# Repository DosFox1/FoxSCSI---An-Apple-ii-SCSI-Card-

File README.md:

# FoxSCSI - An Apple ii SCSI Card 
An open source clone of the Apple ii SCSI Card. Through hole and done in two layers!

(Many thanks to HKZ for testing this VDEV1 Prototype design)

# So what is it?

This is a recreation of the original Apple SCSI Rev C Card for the Apple II.
The equations for the SCSI card were found, converted to GALs, and tested with an original Rev C card.

Additionally, the schematics and ROM for the Rev C card are available online (added in this repository for completeness).
This board is two layer to reduce costs (five boards, finished in ENIG should be about £30 or £6 per board), and is fully through hole.
A 2.85v active termination voltage regulator is added but is not required. 

HKZ is working on an SMD variant of the SCSI card:
https://codeberg.org/hkzlab/AppleII_SCSI_RevC_schematics

# Note Regarding the Board Status
The initial VDEV1 board was tested by HKZ, and three issues were found:
1) a missing connection from IOSEL to the 74LS08
2) A missing "ghost" 330pf capacitor present on the actual boards, but not the transcribed schematics
3) Capacitors were initially noted to be 33pf, actual values should be 330pf.

With these changes, the board successfully booted a DELTA (Apple IIe clone using GALs in place of custom logic - https://codeberg.org/hkzlab/NE_Delta_Schematics).
The latest gerbers have fixes these issues, and should work as is. 

NOTE THAT THEY HAVE NOT BEEN BUILT YET. YOUR MILEAGE MAY VARY!

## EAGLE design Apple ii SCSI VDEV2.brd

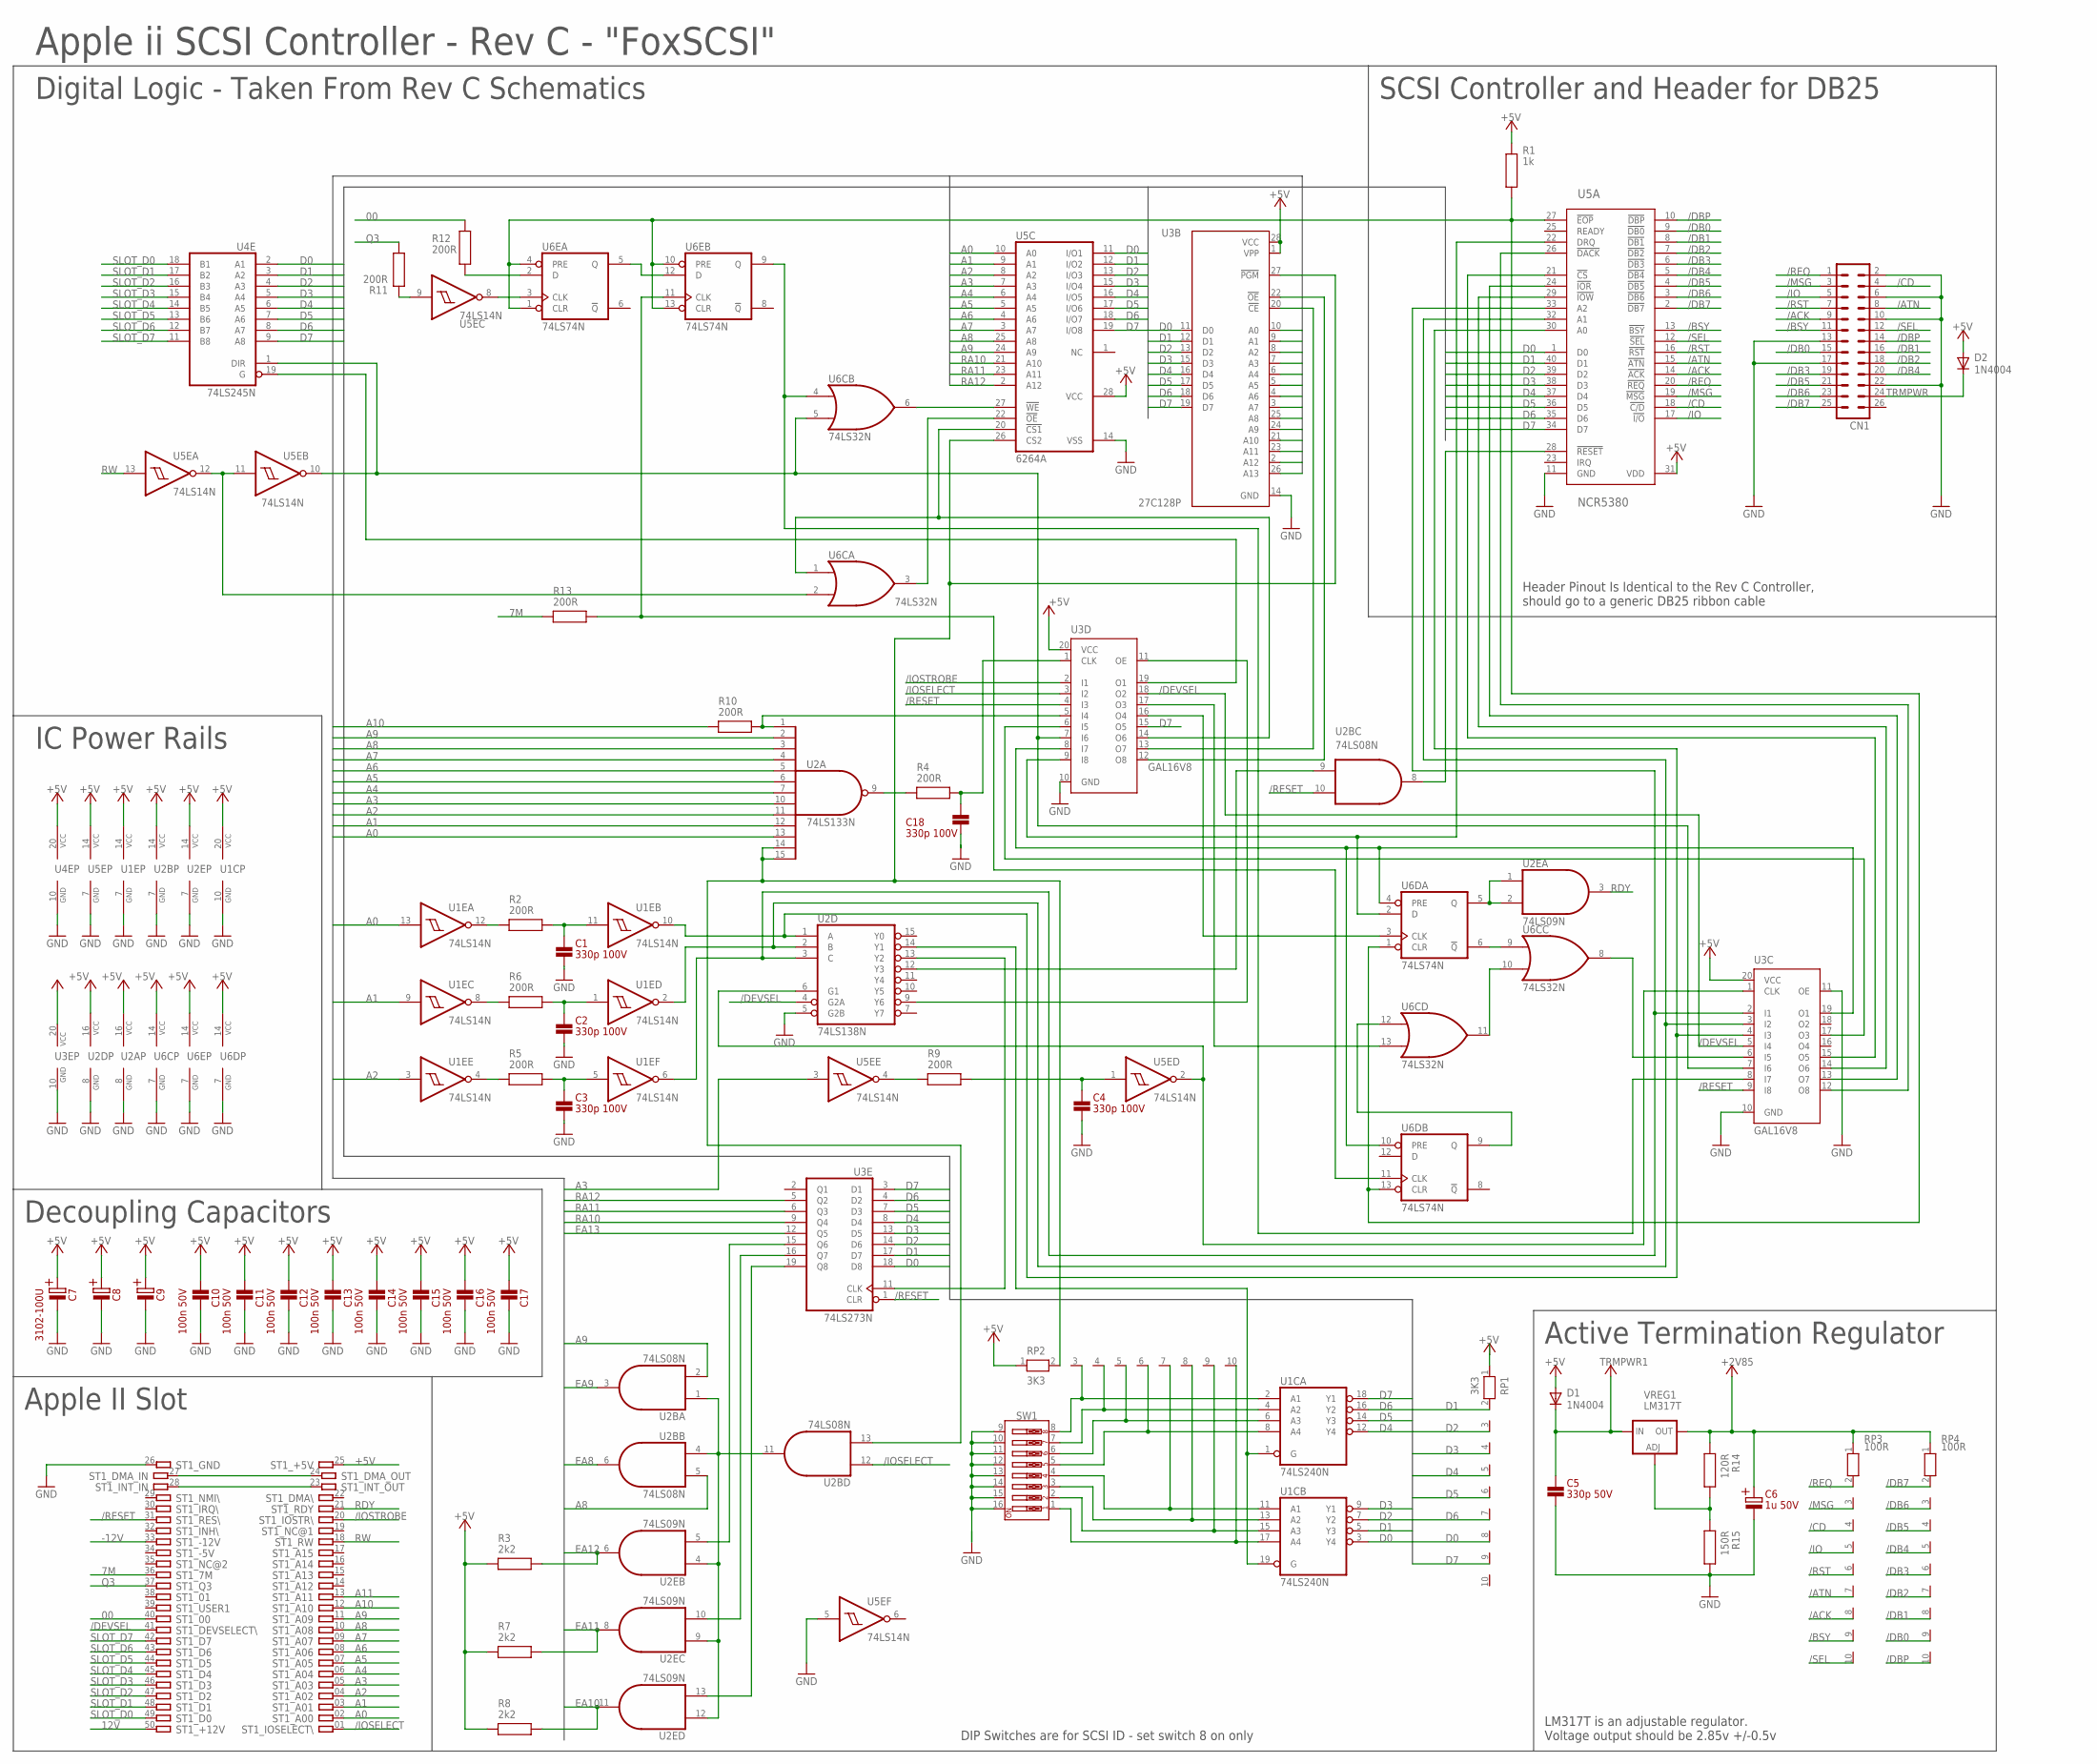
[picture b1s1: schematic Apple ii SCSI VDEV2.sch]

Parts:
C1, C2, C3, C4, C18: 330p 100V; CAP_5.08MM_PITCH
C5: 330p 50V; CAP_5.08MM_PITCH
C6: 1u 50V; CAP_ELECTROLYTIC_FLAT
C7: 3102-100U; CAP_ELECTROLYTIC_FLAT
C8, C9: 10U_TH_ELEC_CAPHORIZONTAL; CAP_ELECTROLYTIC_FLAT
C10, C11, C12, C13, C14, C15, C16, C17: 100n 50V; CAP_5.08MM_PITCH
CN1: MA13-2
D1, D2: 1N4004; DO41-10
R1: 1k; RESISTORTHRUHOLE
R2, R4, R5, R6, R9, R10, R11, R12, R13: 200R; RESISTORTHRUHOLE
R3, R7, R8: 2k2; RESISTORTHRUHOLE
R14: 120R; RESISTORTHRUHOLE
R15: 150R; RESISTORTHRUHOLE
RP1, RP2: 3K3; RN-10
RP3, RP4: 100R; RN-10
ST1: A2-50PINMINI; A2-50PIN-MINI
SW1: DIP-08-PTH; DIPSWITCH-08
U1C: 74LS240N; DIL20
U1E, U5E: 74LS14N; DIL14
U2A: 74LS133N; DIL16
U2B: 74LS08N; DIL14
U2D: 74LS138N; DIL16
U2E: 74LS09N; DIL14
U3B: 27C128P; DIL28-6
U3C, U3D: GAL16V8; DIL20
U3E: 74LS273N; DIL20
U4E: 74LS245N; DIL20
U5A: NCR5380; DIP40
U5C: 6264A; DIL28-6
U6C: 74LS32N; DIL14
U6D, U6E: 74LS74N; DIL14
VREG1: LM317T; 317TL

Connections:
00: R12.P$2, ST1.40
7M: R13.P$1, ST1.36
12V: ST1.50
+2V85: C6.P$1, R14.P$1, RP3.1, RP4.1, VREG1.2 (OUT)
+5V: C7.P$1, C8.P$1, C9.P$1, C10.P$1, C11.P$1, C12.P$1, C13.P$1, C14.P$1, C15.P$1, C16.P$1, C17.P$1, D1.A, D2.A, R1.P$2, R3.P$1, R7.P$1, R8.P$1, RP1.1, RP2.1, ST1.25, U1C.20 (VCC), U1E.14 (VCC), U2A.16 (VCC), U2B.14 (VCC), U2D.16 (VCC), U2E.14 (VCC), U3B.1 (VPP), U3B.28 (VCC), U3C.20 (VCC), U3D.20 (VCC), U3E.20 (VCC), U4E.20 (VCC), U5A.31 (VDD), U5C.28 (VCC), U5E.14 (VCC), U6C.14 (VCC), U6D.14 (VCC), U6E.14 (VCC)
-12V: ST1.33
/ACK: CN1.9, RP3.8, U5A.14 (!ACK)
/ATN: CN1.8, RP3.7, U5A.15 (!ATN)
/BSY: CN1.11, RP3.9, U5A.13 (!BSY)
/CD: CN1.4, RP3.4, U5A.18 (!C/D)
/DB0: CN1.15, RP4.9, U5A.9 (!DB0)
/DB1: CN1.16, RP4.8, U5A.8 (!DB1)
/DB2: CN1.18, RP4.7, U5A.7 (!DB2)
/DB3: CN1.19, RP4.6, U5A.6 (!DB3)
/DB4: CN1.20, RP4.5, U5A.5 (!DB4)
/DB5: CN1.21, RP4.4, U5A.4 (!DB5)
/DB6: CN1.23, RP4.3, U5A.3 (!DB6)
/DB7: CN1.25, RP4.2, U5A.2 (!DB7)
/DBP: CN1.14, RP4.10, U5A.10 (!DBP)
/DEVSEL: ST1.41, U2D.4 (G2A), U3C.5 (I4), U3D.18 (O2)
/IO: CN1.5, RP3.5, U5A.17 (!I/O)
/IOSELECT: ST1.01, U2B.12 (I0), U3D.3 (I2)
/IOSTROBE: ST1.20, U3D.2 (I1)
/MSG: CN1.3, RP3.3, U5A.19 (!MSG)
/REQ: CN1.1, RP3.2, U5A.20 (!REQ)
/RESET: ST1.31, U2B.10 (I1), U3C.9 (I8), U3D.4 (I3), U3E.1 (CLR)
/RST: CN1.7, RP3.6, U5A.16 (!RST)
/SEL: CN1.12, RP3.10, U5A.12 (!SEL)
A0: ST1.02, U1E.13 (I), U2A.13 (I10), U3B.10 (A0), U5C.10 (A0)
A1: ST1.03, U1E.9 (I), U2A.12 (I9), U3B.9 (A1), U5C.9 (A1)
A2: ST1.04, U1E.3 (I), U2A.11 (I8), U3B.8 (A2), U5C.8 (A2)
A3: ST1.05, U2A.10 (I7), U3B.7 (A3), U5C.7 (A3), U5E.3 (I)
A4: ST1.06, U2A.7 (I6), U3B.6 (A4), U5C.6 (A4)
A5: ST1.07, U2A.6 (I5), U3B.5 (A5), U5C.5 (A5)
A6: ST1.08, U2A.5 (I4), U3B.4 (A6), U5C.4 (A6)
A7: ST1.09, U2A.4 (I3), U3B.3 (A7), U5C.3 (A7)
A8: ST1.10, U2A.3 (I2), U2B.5 (I1), U5C.25 (A8)
A9: ST1.11, U2A.2 (I1), U2B.2 (I1), U5C.24 (A9)
A10: R10.P$1, ST1.12
A11: ST1.13
D0: RP1.8, U1C.3 (Y4), U3B.11 (D0), U3E.18 (D8), U4E.2 (A1), U5A.1 (D0), U5C.11 (I/O1)
D1: RP1.2, U1C.5 (Y3), U3B.12 (D1), U3E.17 (D7), U4E.3 (A2), U5A.40 (D1), U5C.12 (I/O2)
D2: RP1.3, U1C.7 (Y2), U3B.13 (D2), U3E.14 (D6), U4E.4 (A3), U5A.39 (D2), U5C.13 (I/O3)
D3: RP1.4, U1C.9 (Y1), U3B.15 (D3), U3E.13 (D5), U4E.5 (A4), U5A.38 (D3), U5C.15 (I/O4)
D4: RP1.5, U1C.12 (Y4), U3B.16 (D4), U3E.8 (D4), U4E.6 (A5), U5A.37 (D4), U5C.16 (I/O5)
D5: RP1.6, U1C.14 (Y3), U3B.17 (D5), U3E.7 (D3), U4E.7 (A6), U5A.36 (D5), U5C.17 (I/O6)
D6: RP1.7, U1C.16 (Y2), U3B.18 (D6), U3E.4 (D2), U4E.8 (A7), U5A.35 (D6), U5C.18 (I/O7)
D7: RP1.9, U1C.18 (Y1), U3B.19 (D7), U3D.15 (O5), U3E.3 (D1), U4E.9 (A8), U5A.34 (D7), U5C.19 (I/O8)
EA8: U2B.6 (O), U3B.25 (A8)
EA9: U2B.3 (O), U3B.24 (A9)
EA10: R8.P$2, U2E.11 (O), U3B.21 (A10)
EA11: R7.P$2, U2E.8 (O), U3B.23 (A11)
EA12: R3.P$2, U2E.6 (O), U3B.2 (A12)
EA13: U3B.26 (A13), U3E.12 (Q5)
GND: C1.P$1, C2.P$1, C3.P$1, C4.P$1, C5.P$1, C6.P$2, C7.P$2, C8.P$2, C9.P$2, C10.P$2, C11.P$2, C12.P$2, C13.P$2, C14.P$2, C15.P$2, C16.P$2, C17.P$2, C18.P$1, CN1.2, CN1.6, CN1.10, CN1.13, CN1.17, CN1.22, R15.P$2, ST1.26, SW1.9, SW1.10, SW1.11, SW1.12, SW1.13, SW1.14, SW1.15, SW1.16, U1C.10 (GND), U1E.7 (GND), U2A.8 (GND), U2B.7 (GND), U2D.5 (G2B), U2D.8 (GND), U2E.7 (GND), U3B.14 (GND), U3C.10 (GND), U3C.11 (OE), U3D.10 (GND), U3E.10 (GND), U4E.10 (GND), U5A.11 (GND), U5C.14 (VSS), U5E.5 (I), U5E.7 (GND), U6C.7 (GND), U6D.7 (GND), U6E.7 (GND)
unnamed: ST1.24, ST1.27
unnamed: ST1.23, ST1.28
unnamed: U5E.11 (I), U5E.12 (O), U6C.2 (I1)
unnamed: U2B.8 (O), U5A.28 (!RESET)
unnamed: RP2.3, SW1.8, U1C.2 (A1)
unnamed: RP2.4, SW1.7, U1C.4 (A2)
unnamed: RP2.5, SW1.6, U1C.6 (A3)
unnamed: RP2.6, SW1.5, U1C.8 (A4)
unnamed: RP2.7, SW1.4, U1C.11 (A1)
unnamed: RP2.8, SW1.3, U1C.13 (A2)
unnamed: RP2.9, SW1.2, U1C.15 (A3)
unnamed: RP2.10, SW1.1, U1C.17 (A4)
unnamed: U2E.13 (I1), U3E.19 (Q8)
unnamed: U2B.1 (I0), U2B.4 (I0), U2B.11 (O), U2E.4 (I0), U2E.9 (I0), U2E.12 (I0)
unnamed: U2E.10 (I1), U3E.16 (Q7)
unnamed: U2E.5 (I1), U3E.15 (Q6)
unnamed: U1E.10 (O), U2D.1 (A), U3C.4 (I3), U5A.30 (A0)
unnamed: U1E.2 (O), U2D.2 (B), U3C.3 (I2), U5A.32 (A1)
unnamed: C18.P$2, R4.P$2, U3D.1 (CLK)
unnamed: C1.P$2, R2.P$2, U1E.11 (I)
unnamed: R2.P$1, U1E.12 (O)
unnamed: R6.P$1, U1E.8 (O)
unnamed: C2.P$2, R6.P$2, U1E.1 (I)
unnamed: C3.P$2, R5.P$2, U1E.5 (I)
unnamed: R5.P$1, U1E.4 (O)
unnamed: R9.P$1, U5E.4 (O)
unnamed: C4.P$2, R9.P$2, U5E.1 (I)
unnamed: R4.P$1, U2A.9 (O)
unnamed: R10.P$2, U2A.1 (I0), U3D.5 (I4)
unnamed: U1E.6 (O), U2D.3 (C), U3C.2 (I1), U5A.33 (A2)
unnamed: U3C.17 (O3), U3D.6 (I5)
unnamed: U3C.8 (I7), U6C.4 (I0), U6E.9 (Q)
unnamed: U3C.19 (O1), U3D.8 (I7), U6D.4 (PRE), U6D.10 (PRE)
unnamed: U3D.9 (I8), U5A.22 (DRQ), U6D.2 (D)
unnamed: U2D.9 (Y6), U3D.11 (OE)
unnamed: U3B.22 (!OE), U3D.12 (O8)
unnamed: U3B.20 (!CE), U3D.13 (O7)
unnamed: U3D.14 (O6), U5C.20 (!CS1), U6C.1 (I0)
unnamed: U3D.16 (O4), U6D.3 (CLK)
unnamed: U3D.17 (O3), U6C.13 (I1)
unnamed: U3D.19 (O1), U4E.19 (G)
unnamed: U2D.6 (G1), U3C.1 (CLK), U5E.2 (O)
unnamed: U2D.13 (Y2), U3E.11 (CLK)
unnamed: U2B.9 (I0), U2D.12 (Y3)
unnamed: U1C.1 (G), U1C.19 (G), U2D.14 (Y1)
unnamed: U2E.1 (I0), U2E.2 (I1), U6D.5 (Q)
unnamed: U3C.6 (I5), U6C.8 (O)
unnamed: U6C.9 (I0), U6D.6 (!Q)
unnamed: U6C.10 (I1), U6C.11 (O)
unnamed: U6C.12 (I0), U6D.9 (Q)
unnamed: R1.P$1, U5A.27 (!EOP), U6D.1 (CLR), U6D.13 (CLR), U6E.1 (CLR), U6E.4 (PRE), U6E.10 (PRE), U6E.13 (CLR)
unnamed: R13.P$2, U6D.11 (CLK), U6E.11 (CLK)
unnamed: R11.P$2, U5E.9 (I)
unnamed: U3C.14 (O6), U5A.29 (!IOW)
unnamed: U3C.13 (O7), U5A.24 (!IOR)
unnamed: U3C.12 (O8), U5A.26 (!DACK)
unnamed: U3C.7 (I6), U3D.7 (I6), U4E.1 (DIR), U5E.10 (O), U6C.5 (I1)
unnamed: U3C.15 (O5), U5A.21 (!CS)
unnamed: U5E.8 (O), U6E.3 (CLK)
unnamed: R12.P$1, U6E.2 (D)
unnamed: U6E.5 (Q), U6E.12 (D)
unnamed: U5C.27 (!WE), U6C.6 (O)
unnamed: U5C.22 (!OE), U6C.3 (O)
unnamed: RP2.2, U2A.14 (I11), U2A.15 (I12), U2B.13 (I1), U3B.27 (!PGM), U5C.26 (CS2)
unnamed: R14.P$2, R15.P$1, VREG1.1 (ADJ)
Q3: R11.P$1, ST1.37
RA10: U3E.9 (Q4), U5C.21 (A10)
RA11: U3E.6 (Q3), U5C.23 (A11)
RA12: U3E.5 (Q2), U5C.2 (A12)
RDY: ST1.21, U2E.3 (O)
RW: ST1.18, U5E.13 (I)
SLOT_D0: ST1.49, U4E.18 (B1)
SLOT_D1: ST1.48, U4E.17 (B2)
SLOT_D2: ST1.47, U4E.16 (B3)
SLOT_D3: ST1.46, U4E.15 (B4)
SLOT_D4: ST1.45, U4E.14 (B5)
SLOT_D5: ST1.44, U4E.13 (B6)
SLOT_D6: ST1.43, U4E.12 (B7)
SLOT_D7: ST1.42, U4E.11 (B8)
TRMPWR: CN1.24, D2.C
TRMPWR1: C5.P$2, D1.C, VREG1.3 (IN)

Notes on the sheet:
Apple ii SCSI Controller - Rev C - "FoxSCSI"
Digital Logic - Taken From Rev C Schematics
Apple II Slot
Active Termination Regulator
SCSI Controller and Header for DB25
Header Pinout Is Identical to the Rev C Controller, should go to a generic DB25 ribbon cable
LM317T is an adjustable regulator. Voltage output should be 2.85v +/-0.5v
DIP Switches are for SCSI ID - set switch 8 on only
Decoupling Capacitors
IC Power Rails

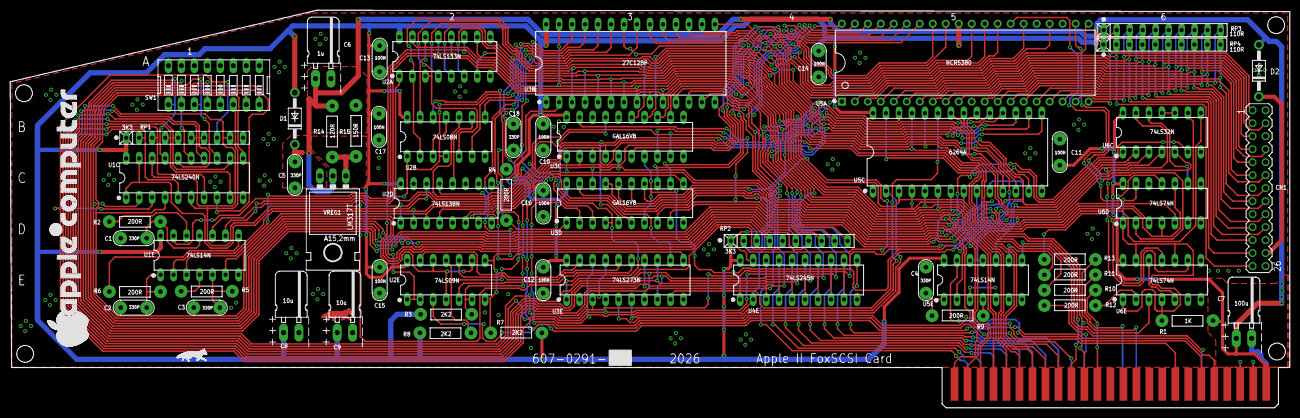
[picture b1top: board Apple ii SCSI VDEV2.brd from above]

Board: 2 copper layers, 250.3 x 77.8 mm, 60 parts (0 on the bottom side), 133 nets.

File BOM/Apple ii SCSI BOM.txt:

Partlist

Exported from Apple ii SCSI VDEV2.sch at 25/Mar/26 09:02

EAGLE Version 9.6.2 Copyright (c) 1988-2020 Autodesk, Inc.

Assembly variant: 

Part     Value          Device                     Package               Library           Sheet

C1       330p 100V      330P_TH_CAP                 CAP_5.08MM_PITCH      Capacitors TH     1
C2       330p 100V      330P_TH_CAP                 CAP_5.08MM_PITCH      Capacitors TH     1
C3       330p 100V      330P_TH_CAP                 CAP_5.08MM_PITCH      Capacitors TH     1
C4       330p 100V      330P_TH_CAP                 CAP_5.08MM_PITCH      Capacitors TH     1
C5       330p 50V       330P_TH_CAP                CAP_5.08MM_PITCH      Capacitors TH     1
C6       1u 50V         1U_TH_ELEC_CAPHORIZONTAL   CAP_ELECTROLYTIC_FLAT Capacitors TH     1
C7       100U 50v       100U_TH_ELEC_CAPHORIZONTAL CAP_ELECTROLYTIC_FLAT Capacitors TH     1
C8       10U 50v        10U_TH_ELEC_CAPHORIZONTAL  CAP_ELECTROLYTIC_FLAT Capacitors TH     1
C9       10U 50v        10U_TH_ELEC_CAPHORIZONTAL  CAP_ELECTROLYTIC_FLAT Capacitors TH     1
C10      100n 50V       100N_TH_CAP                CAP_5.08MM_PITCH      Capacitors TH     1
C11      100n 50V       100N_TH_CAP                CAP_5.08MM_PITCH      Capacitors TH     1
C12      100n 50V       100N_TH_CAP                CAP_5.08MM_PITCH      Capacitors TH     1
C13      100n 50V       100N_TH_CAP                CAP_5.08MM_PITCH      Capacitors TH     1
C14      100n 50V       100N_TH_CAP                CAP_5.08MM_PITCH      Capacitors TH     1
C15      100n 50V       100N_TH_CAP                CAP_5.08MM_PITCH      Capacitors TH     1
C16      100n 50V       100N_TH_CAP                CAP_5.08MM_PITCH      Capacitors TH     1
C17      100n 50V       100N_TH_CAP                CAP_5.08MM_PITCH      Capacitors TH     1
C18      330p 100V      33P_TH_CAP                 CAP_5.08MM_PITCH      Capacitors TH     1
CN1      2x13 header    MA13-2                     MA13-2                con-lstb          1
D1       1N4004         1N4004                     DO41-10               adafruit          1
D2       1N4004         1N4004                     DO41-10               adafruit          1
R1       1k             1K_TH_RESISTOR             RESISTORTHRUHOLE      Resistors TH      1
R2       200R           200R_TH_RESISTOR           RESISTORTHRUHOLE      Resistors TH      1
R3       2k2            2K2_TH_RESISTOR            RESISTORTHRUHOLE      Resistors TH      1
R4       200R           200R_TH_RESISTOR           RESISTORTHRUHOLE      Resistors TH      1
R5       200R           200R_TH_RESISTOR           RESISTORTHRUHOLE      Resistors TH      1
R6       200R           200R_TH_RESISTOR           RESISTORTHRUHOLE      Resistors TH      1
R7       2k2            2K2_TH_RESISTOR            RESISTORTHRUHOLE      Resistors TH      1
R8       2k2            2K2_TH_RESISTOR            RESISTORTHRUHOLE      Resistors TH      1
R9       200R           200R_TH_RESISTOR           RESISTORTHRUHOLE      Resistors TH      1
R10      200R           200R_TH_RESISTOR           RESISTORTHRUHOLE      Resistors TH      1
R11      200R           200R_TH_RESISTOR           RESISTORTHRUHOLE      Resistors TH      1
R12      200R           200R_TH_RESISTOR           RESISTORTHRUHOLE      Resistors TH      1
R13      200R           200R_TH_RESISTOR           RESISTORTHRUHOLE      Resistors TH      1
R14      120R           120R_TH_RESISTOR           RESISTORTHRUHOLE      Resistors TH      1
R15      150R           150R_TH_RESISTOR           RESISTORTHRUHOLE      Resistors TH      1
RP1      3K3            RN09                       RN-10                 resistor-net      1
RP2      3K3            RN09                       RN-10                 resistor-net      1
RP3      100R           RN09                       RN-10                 resistor-net      1
RP4      100R           RN09                       RN-10                 resistor-net      1
SW1      8xDip Switch   DIP-08-PTH                 DIPSWITCH-08          SparkFun-Switches 1
U1C      74LS240N       74LS240N                   DIL20                 74xx-us           1
U1E      74LS14N        74LS14N                    DIL14                 74xx-us           1
U2A      74LS133N       74LS133N                   DIL16                 74xx-us           1
U2B      74LS08N        74LS08N                    DIL14                 74xx-us           1
U2D      74LS138N       74LS138N                   DIL16                 74xx-us           1
U2E      74LS09N        74LS09N                    DIL14                 74xx-us           1
U3B      27C128P        27C128P                    DIL28-6               microchip         1
U3C      GAL16V8        ATF16V8BP3                 DIL20                 atmel             1
U3D      GAL16V8        ATF16V8BP3                 DIL20                 atmel             1
U3E      74LS273N       74273N                     DIL20                 74xx-eu           1
U4E      74LS245N       74LS245N                   DIL20                 74xx-us           1
U5A      NCR5380        NCR5380                    DIP40                 ICs               1
U5C      6264A          6264A                      DIL28-6               memory-hitachi    1
U5E      74LS14N        74LS14N                    DIL14                 74xx-us           1
U6C      74LS32N        74LS32N                    DIL14                 74xx-us           1
U6D      74LS74N        74LS74N                    DIL14                 74xx-us           1
U6E      74LS74N        74LS74N                    DIL14                 74xx-us           1
VREG1    LM317T         LM317TL                    317TL                 v-reg             1

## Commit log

2026-03-26 Rename Apple ii FoxSCSI Gerbers VDEV2.3 JLCPCB.zip to Gerbers/Apple ii FoxSCSI Gerbers VDEV2.3 JLCPCB.zip
2026-03-26 Rename U3D_U14_342-0416-A.jed to PAL Equations/U3D_U14_342-0416-A.jed
2026-03-26 Rename U3C_U3_342-0415-A.jed to PAL Equations/ U3C_U3_342-0415-A.jed
2026-03-26 Rename U3D_U14_342-0416-A.eqn to PAL Equations/U3D_U14_342-0416-A.eqn
2026-03-26 Rename U3C_U3_342-0415-A.eqn to PAL Equations/U3C_U3_342-0415-A.eqn
2026-03-26 Rename Rev. C SCSI Schematic.jpg to Schematics/Rev. C SCSI Schematic.jpg
2026-03-26 Rename Apple ii FoxSCSI schematic.pdf to Schematics/Apple ii FoxSCSI schematic.pdf
2026-03-26 Rename Apple ii SCSI BOM.txt to BOM/Apple ii SCSI BOM.txt
2026-03-26 Rename Apple Logo.svg to Renders/Apple Logo.svg
2026-03-26 Rename Apple ii SCSI Hi Res Bottom Side.png to Renders/Apple ii SCSI Hi Res Bottom Side.png
2026-03-26 Rename Apple ii SCSI Hi Res Top Side.png to Renders/Apple ii SCSI Hi Res Top Side.png
2026-03-26 Rename Apple ii SCSI Low Res Bottom Side.png to Renders/Apple ii SCSI Low Res Bottom Side.png
2026-03-26 Rename Apple ii SCSI Low Res Top Side.png to Renders/Apple ii SCSI Low Res Top Side.png
2026-03-26 Rename Apple ii SCSI VDEV2 SVG Renders.zip to Renders/Apple ii SCSI VDEV2 SVG Renders.zip
2026-03-26 Rename Apple ii SCSI VDEV2.brd to Design Files/Apple ii SCSI VDEV2.brd
2026-03-26 Rename Apple ii SCSI VDEV2.sch to Design Files/Apple ii SCSI VDEV2.sch
2026-03-31 Add files via upload
    Added ROM

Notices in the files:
Apple ii SCSI VDEV2.brd:
Released under CERN-OHL-P
parts and their libraries:
SparkFun-Switches: Licensing: Creative Commons ShareAlike 4.0 International - https://creativecommons.org/licenses/by-sa/4.0
